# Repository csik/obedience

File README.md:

# obedience

Hacking around an aestheticized experiment.

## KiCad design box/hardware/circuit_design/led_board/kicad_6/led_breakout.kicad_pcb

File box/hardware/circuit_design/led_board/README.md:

# LED Driver Board Set

### Meant to be used as a set of two identical boards
- Each board can drive up to 16 LEDs
- The first board connects to the Raspberry Pi
- The second is daisy chained with a jumper
- Besides the 30 main Milgram voltage LEDs, 2 auxilliary LEDs are available on the second board
- A small `3V3 OK` LED on the board illuminates when the board has power

### An optional `VBUS` connection is available for driving the LEDS with a different DC voltage source
- Select the DC voltage source with a solder jumper
- The `3V3` setting is typical
- The `VBUS` setting is included in case there are issues with driving the LEDs from the Raspberry Pi power supply
- Note that the `VBUS OK` LED will only light up if there is a DC source connected to `VBUS`
  - it is normal for this LED to be dim if using the `3V3` DC source

### View from the back

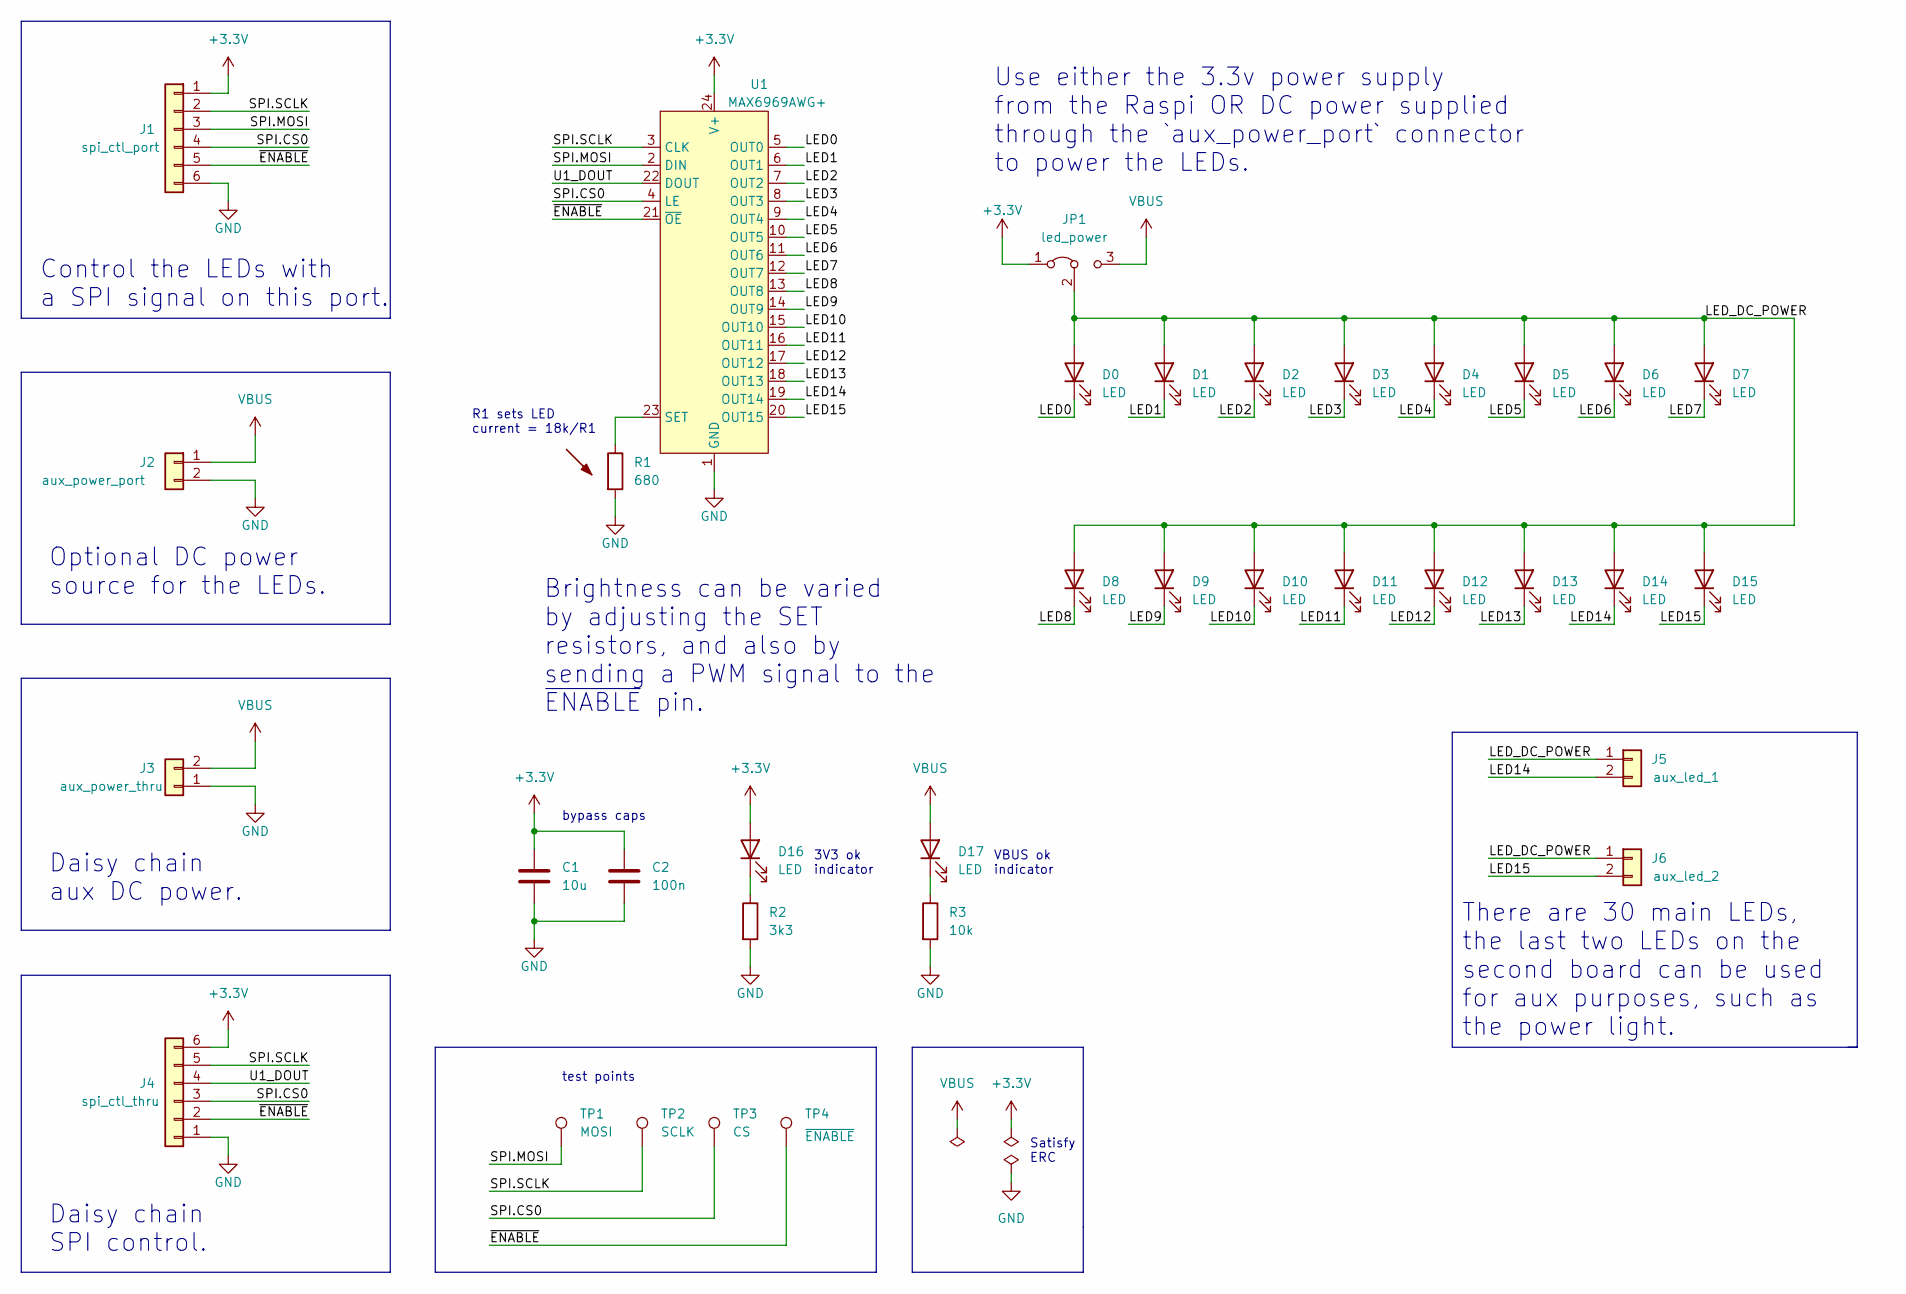
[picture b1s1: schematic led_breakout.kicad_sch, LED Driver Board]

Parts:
C1: 10u; C_0805_2012Metric
C2: 100n; C_0805_2012Metric
D0, D1, D2, D3, D4, D5, D6, D7, D8, D9, D10, D11, D12, D13, D14, D15: LED; LED_D5.0mm
D16, D17: LED; LED_0805_2012Metric
J1: spi_ctl_port; Molex_KK-254_AE-6410-06A_1x06_P2.54mm_Vertical
J2: aux_power_port; Molex_KK-254_AE-6410-02A_1x02_P2.54mm_Vertical
J3: aux_power_thru; Molex_KK-254_AE-6410-02A_1x02_P2.54mm_Vertical
J4: spi_ctl_thru; Molex_KK-254_AE-6410-06A_1x06_P2.54mm_Vertical
J5: aux_led_1; Molex_KK-254_AE-6410-02A_1x02_P2.54mm_Vertical
J6: aux_led_2; Molex_KK-254_AE-6410-02A_1x02_P2.54mm_Vertical
JP1: led_power; SolderJumper-3_P2.0mm_Open_TrianglePad1.0x1.5mm
R1: 680; R_0805_2012Metric
R2: 3k3; R_0805_2012Metric
R3: 10k; R_0805_2012Metric
TP1: MOSI; TestPoint_Keystone_5000-5004_Miniature
TP2: SCLK; TestPoint_Keystone_5000-5004_Miniature
TP3: CS; TestPoint_Keystone_5000-5004_Miniature
TP4: ~{ENABLE}; TestPoint_Keystone_5000-5004_Miniature
U1: MAX6969AWG+; SOIC-24W_7.5x15.4mm_P1.27mm

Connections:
+3.3V: C1.1, C2.1, D16.2 (A), J1.1, J4.6, JP1.1 (A), U1.24 (V+)
/LED0: D0.1 (K), U1.5 (OUT0)
/LED1: D1.1 (K), U1.6 (OUT1)
/LED2: D2.1 (K), U1.7 (OUT2)
/LED3: D3.1 (K), U1.8 (OUT3)
/LED4: D4.1 (K), U1.9 (OUT4)
/LED5: D5.1 (K), U1.10 (OUT5)
/LED6: D6.1 (K), U1.11 (OUT6)
/LED7: D7.1 (K), U1.12 (OUT7)
/LED8: D8.1 (K), U1.13 (OUT8)
/LED9: D9.1 (K), U1.14 (OUT9)
/LED10: D10.1 (K), U1.15 (OUT10)
/LED11: D11.1 (K), U1.16 (OUT11)
/LED12: D12.1 (K), U1.17 (OUT12)
/LED13: D13.1 (K), U1.18 (OUT13)
/LED14: D14.1 (K), J5.2, U1.19 (OUT14)
/LED15: D15.1 (K), J6.2, U1.20 (OUT15)
/LED_DC_POWER: D0.2 (A), D1.2 (A), D2.2 (A), D3.2 (A), D4.2 (A), D5.2 (A), D6.2 (A), D7.2 (A), D8.2 (A), D9.2 (A), D10.2 (A), D11.2 (A), D12.2 (A), D13.2 (A), D14.2 (A), D15.2 (A), J5.1, J6.1, JP1.2 (C)
/SPI.CS0: J1.4, J4.3, TP3.1, U1.4 (LE)
/SPI.MOSI: J1.3, TP1.1, U1.2 (DIN)
/SPI.SCLK: J1.2, J4.5, TP2.1, U1.3 (CLK)
/U1_DOUT: J4.4, U1.22 (DOUT)
/~ENABLE: J1.5, J4.2, TP4.1, U1.21 (~OE)
GND: C1.2, C2.2, J1.6, J2.2, J3.1, J4.1, R1.2, R2.2, R3.2, U1.1 (GND)
unnamed: D16.1 (K), R2.1
unnamed: D17.1 (K), R3.1
unnamed: R1.1, U1.23 (SET)
VBUS: D17.2 (A), J2.1, J3.2, JP1.3 (B)

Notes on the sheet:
R1 sets LED current = 18k/R1
3V3 ok indicator
Optional DC power source for the LEDs.
There are 30 main LEDs, the last two LEDs on the second board can be used for aux purposes, such as the power light.
Brightness can be varied by adjusting the SET resistors, and also by sending a PWM signal to the ~{ENABLE} pin.
Use either the 3.3v power supply from the Raspi OR DC power supplied through the `aux_power_port` connector to power the LEDs.
bypass caps
Control the LEDs with a SPI signal on this port.
Daisy chain aux DC power.
Satisfy ERC
test points
Daisy chain SPI control.
VBUS ok indicator

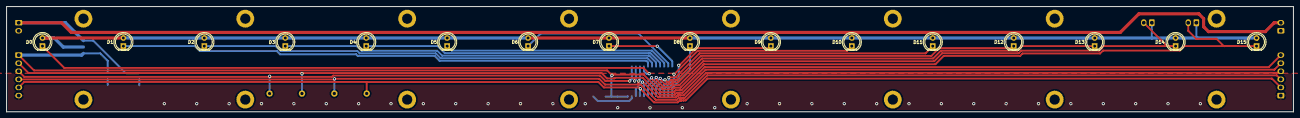
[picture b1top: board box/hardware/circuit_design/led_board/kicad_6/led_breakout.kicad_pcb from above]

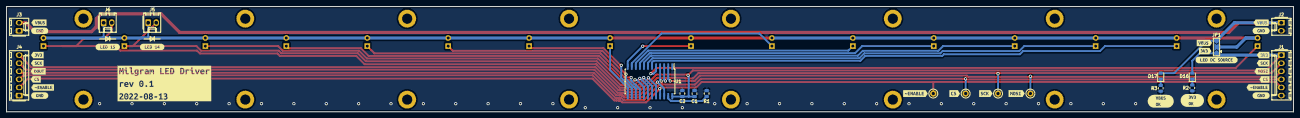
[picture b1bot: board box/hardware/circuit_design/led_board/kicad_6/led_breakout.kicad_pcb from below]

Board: 2 copper layers, 403.9 x 33.0 mm, 63 parts (47 on the bottom side), 28 nets.

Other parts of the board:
kibuzzard-62C08D9D: G***; kibuzzard-62C08D9D
kibuzzard-62C08DB4: G***; kibuzzard-62C08DB4
kibuzzard-62C080C4, kibuzzard-62C080C4#2, kibuzzard-62C080C4#3, kibuzzard-62C080C4#4: G***; kibuzzard-62C080C4
kibuzzard-62C080FF, kibuzzard-62C080FF#2: G***; kibuzzard-62C080FF
kibuzzard-62C081B4, kibuzzard-62C081B4#2: G***; kibuzzard-62C081B4
kibuzzard-62C081F9: G***; kibuzzard-62C081F9
kibuzzard-62C098AA: G***; kibuzzard-62C098AA
kibuzzard-62C098B9: G***; kibuzzard-62C098B9
kibuzzard-62C0819F, kibuzzard-62C0819F#2: G***; kibuzzard-62C0819F
kibuzzard-62C0832C: G***; kibuzzard-62C0832C
kibuzzard-62C0833D: G***; kibuzzard-62C0833D
kibuzzard-62C08177, kibuzzard-62C08177#2: G***; kibuzzard-62C08177
kibuzzard-62C08184, kibuzzard-62C08184#2: G***; kibuzzard-62C08184
kibuzzard-62C08194: G***; kibuzzard-62C08194
kibuzzard-62C08351: G***; kibuzzard-62C08351
kibuzzard-62F7B6AB: G***; kibuzzard-62F7B6AB
kibuzzard-62F7B6F0: G***; kibuzzard-62F7B6F0
kibuzzard-62F7B661: G***; kibuzzard-62F7B661
kibuzzard-62F7B788: G***; kibuzzard-62F7B788
kibuzzard-62F7B810: G***; kibuzzard-62F7B810

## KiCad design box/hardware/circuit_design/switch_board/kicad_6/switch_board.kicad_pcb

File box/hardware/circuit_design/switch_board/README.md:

# Switch Reader Board Set

### Meant to be used as a set of two identical boards
- Each board can read up to 16 switches
- The first board connects to the Raspberry Pi
- The second is daisy chained with a jumper
- Besides the 30 main Milgram voltage switches, 4 auxilliary switches are available on the second board
- A small `3V3 OK` LED on the board illuminates when the board has power
- Note that you don't need to solder every switch lug, only 1 of the switch poles is wired

### The I2C addresses must be set with solder jumpers
- These jumpers make up the low 3-bits of the binary address for each PC9555 chip
- The most likely pattern, looking from left to right is: `0b010, 0b011, 0b000, 0b001`
  - this matches the addresses in the demo function of `[0x20, 0x21, 0x22, 0x23]`
- Valid addresses for the chips are in `[0x20..0x27]`
  - the `2` in the upper byte is fixed, and the lower byte can be changed 
- Other addresses are possible if more I2C devices are added and there is an address collision

### View from the back

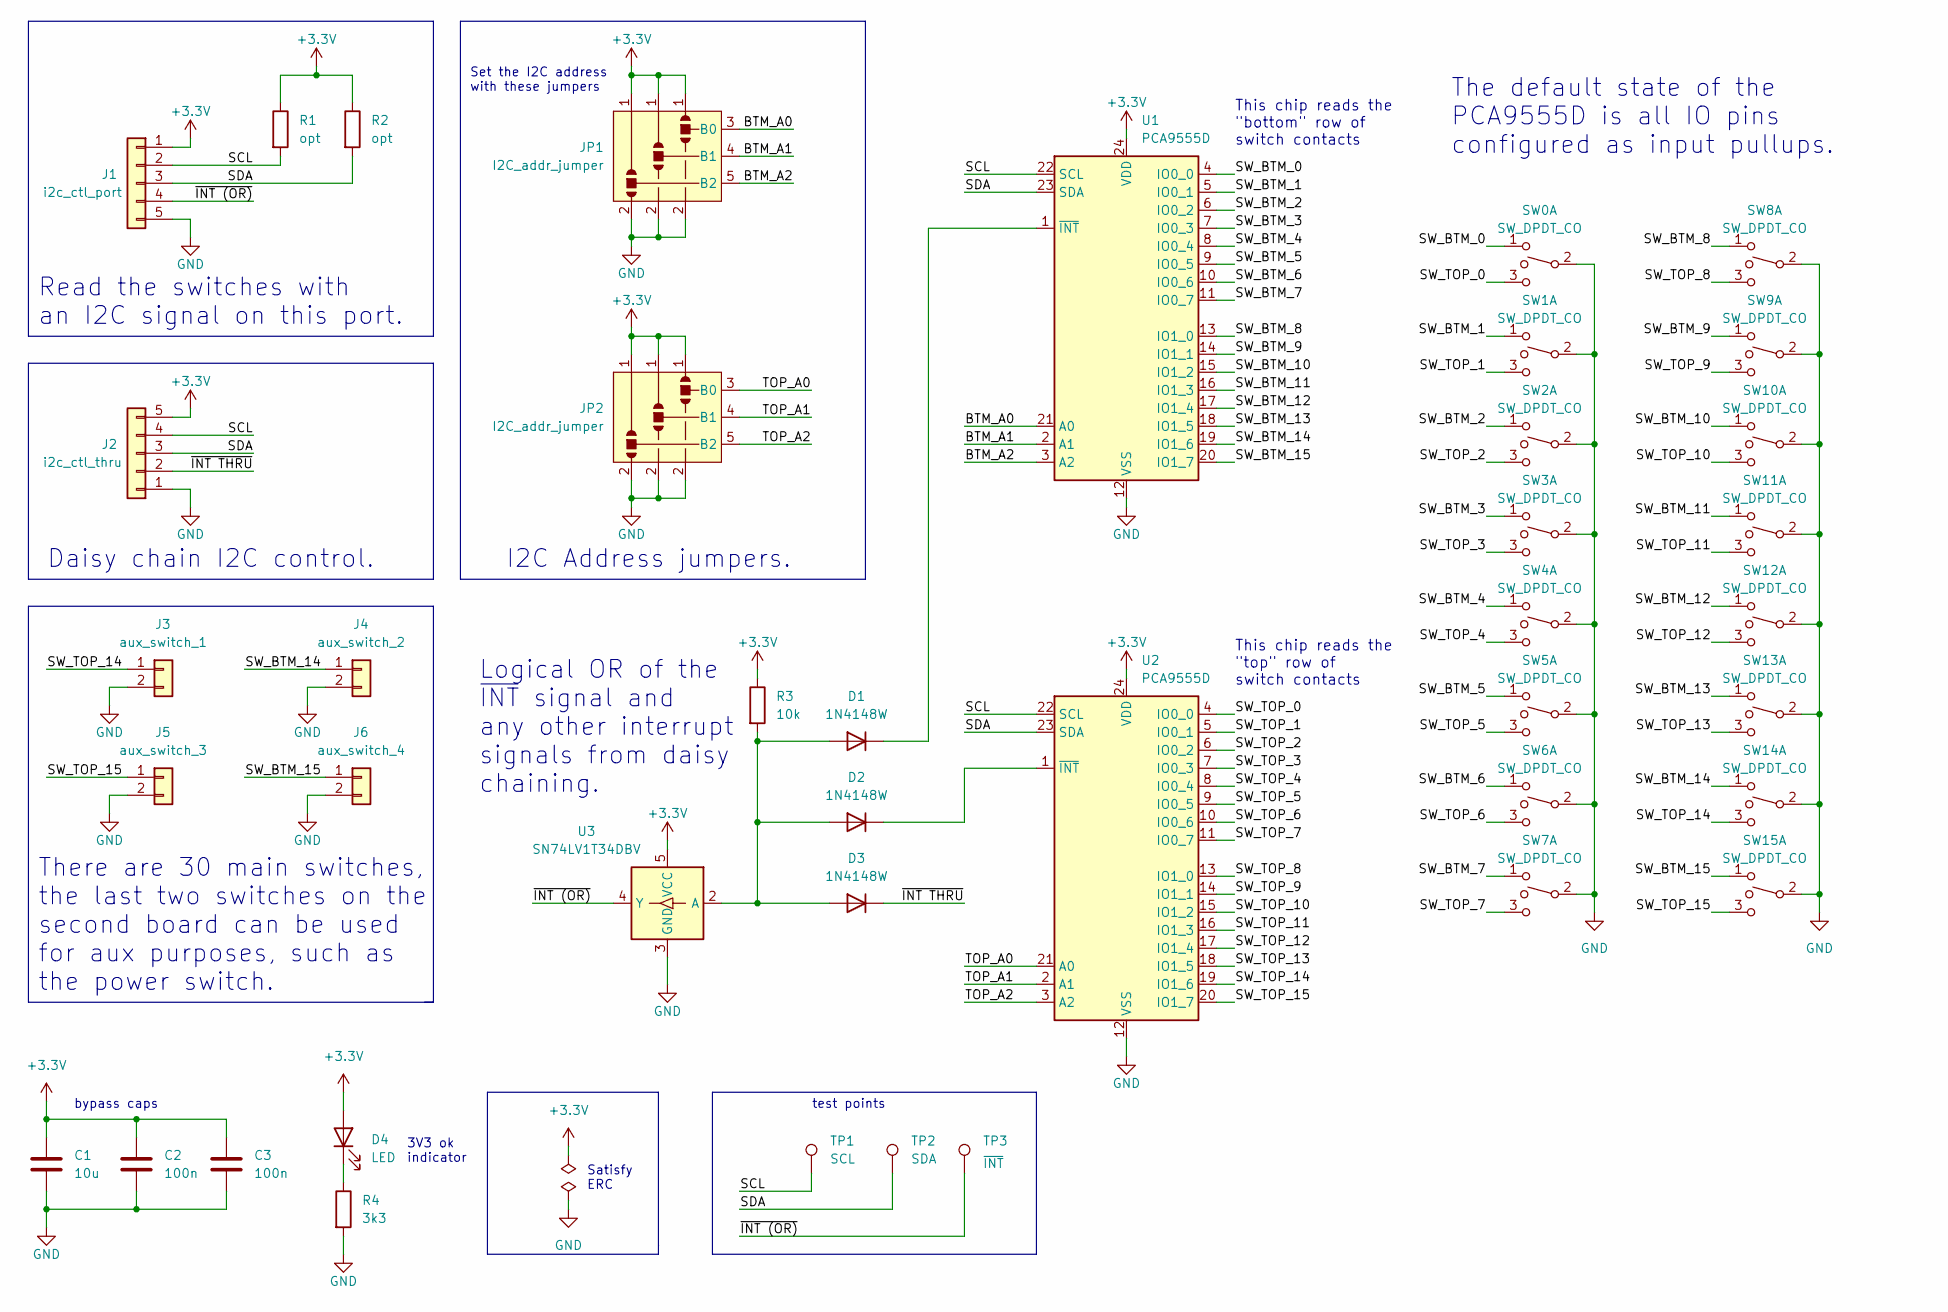
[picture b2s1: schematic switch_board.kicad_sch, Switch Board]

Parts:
C1: 10u; C_0805_2012Metric
C2, C3: 100n; C_0805_2012Metric
D1, D2, D3: 1N4148W; D_SOD-123
D4: LED; LED_0805_2012Metric
J1: i2c_ctl_port; Molex_KK-254_AE-6410-05A_1x05_P2.54mm_Vertical
J2: i2c_ctl_thru; Molex_KK-254_AE-6410-05A_1x05_P2.54mm_Vertical
J3: aux_switch_1; Molex_KK-254_AE-6410-02A_1x02_P2.54mm_Vertical
J4: aux_switch_2; Molex_KK-254_AE-6410-02A_1x02_P2.54mm_Vertical
J5: aux_switch_3; Molex_KK-254_AE-6410-02A_1x02_P2.54mm_Vertical
J6: aux_switch_4; Molex_KK-254_AE-6410-02A_1x02_P2.54mm_Vertical
JP1, JP2: I2C_addr_jumper
R1, R2: opt; R_0805_2012Metric
R3: 10k; R_0805_2012Metric
R4: 3k3; R_0805_2012Metric
SW0, SW1, SW2, SW3, SW4, SW5, SW6, SW7, SW8, SW9, SW10, SW11, SW12, SW13, SW14, SW15: SW_DPDT_CO; orange_DPDT
TP1: SCL; TestPoint_Keystone_5000-5004_Miniature
TP2: SDA; TestPoint_Keystone_5000-5004_Miniature
TP3: ~{INT}; TestPoint_Keystone_5000-5004_Miniature
U1, U2: PCA9555D; SOIC-24W_7.5x15.4mm_P1.27mm
U3: SN74LV1T34DBV; SOT-23-5

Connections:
+3.3V: C1.1, C2.1, C3.1, D4.2 (A), J1.1, J2.5, JP1.1, JP2.1, R1.1, R2.1, R3.1, U1.24 (VDD), U2.24 (VDD), U3.5 (VCC)
/BTM_A0: JP1.3 (B0), U1.21 (A0)
/BTM_A1: JP1.4 (B1), U1.2 (A1)
/BTM_A2: JP1.5 (B2), U1.3 (A2)
/SCL: J1.2, J2.4, R1.2, TP1.1, U1.22 (SCL), U2.22 (SCL)
/SDA: J1.3, J2.3, R2.2, TP2.1, U1.23 (SDA), U2.23 (SDA)
/SW_BTM_0: SW0.1, U1.4 (IO0_0)
/SW_BTM_1: SW1.1, U1.5 (IO0_1)
/SW_BTM_2: SW2.1, U1.6 (IO0_2)
/SW_BTM_3: SW3.1, U1.7 (IO0_3)
/SW_BTM_4: SW4.1, U1.8 (IO0_4)
/SW_BTM_5: SW5.1, U1.9 (IO0_5)
/SW_BTM_6: SW6.1, U1.10 (IO0_6)
/SW_BTM_7: SW7.1, U1.11 (IO0_7)
/SW_BTM_8: SW8.1, U1.13 (IO1_0)
/SW_BTM_9: SW9.1, U1.14 (IO1_1)
/SW_BTM_10: SW10.1, U1.15 (IO1_2)
/SW_BTM_11: SW11.1, U1.16 (IO1_3)
/SW_BTM_12: SW12.1, U1.17 (IO1_4)
/SW_BTM_13: SW13.1, U1.18 (IO1_5)
/SW_BTM_14: J4.1, SW14.1, U1.19 (IO1_6)
/SW_BTM_15: J6.1, SW15.1, U1.20 (IO1_7)
/SW_TOP_0: SW0.3, U2.4 (IO0_0)
/SW_TOP_1: SW1.3, U2.5 (IO0_1)
/SW_TOP_2: SW2.3, U2.6 (IO0_2)
/SW_TOP_3: SW3.3, U2.7 (IO0_3)
/SW_TOP_4: SW4.3, U2.8 (IO0_4)
/SW_TOP_5: SW5.3, U2.9 (IO0_5)
/SW_TOP_6: SW6.3, U2.10 (IO0_6)
/SW_TOP_7: SW7.3, U2.11 (IO0_7)
/SW_TOP_8: SW8.3, U2.13 (IO1_0)
/SW_TOP_9: SW9.3, U2.14 (IO1_1)
/SW_TOP_10: SW10.3, U2.15 (IO1_2)
/SW_TOP_11: SW11.3, U2.16 (IO1_3)
/SW_TOP_12: SW12.3, U2.17 (IO1_4)
/SW_TOP_13: SW13.3, U2.18 (IO1_5)
/SW_TOP_14: J3.1, SW14.3, U2.19 (IO1_6)
/SW_TOP_15: J5.1, SW15.3, U2.20 (IO1_7)
/TOP_A0: JP2.3 (B0), U2.21 (A0)
/TOP_A1: JP2.4 (B1), U2.2 (A1)
/TOP_A2: JP2.5 (B2), U2.3 (A2)
/~INT (OR): J1.4, TP3.1, U3.4 (Y)
/~INT THRU: D3.1 (K), J2.2
GND: C1.2, C2.2, C3.2, J1.5, J2.1, J3.2, J4.2, J5.2, J6.2, JP1.2, JP2.2, R4.2, SW0.2, SW1.2, SW2.2, SW3.2, SW4.2, SW5.2, SW6.2, SW7.2, SW8.2, SW9.2, SW10.2, SW11.2, SW12.2, SW13.2, SW14.2, SW15.2, U1.12 (VSS), U2.12 (VSS), U3.3 (GND)
unnamed: D1.1 (K), U1.1 (~INT)
unnamed: D1.2 (A), D2.2 (A), D3.2 (A), R3.2, U3.2 (A)
unnamed: D2.1 (K), U2.1 (~INT)
unnamed: D4.1 (K), R4.1

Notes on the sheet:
I2C Address jumpers.
3V3 ok indicator
Set the I2C address with these jumpers
This chip reads the "top" row of switch contacts
This chip reads the "bottom" row of switch contacts
bypass caps
Read the switches with an I2C signal on this port.
Satisfy ERC
The default state of the PCA9555D is all IO pins configured as input pullups.
Logical OR of the ~{INT} signal and any other interrupt signals from daisy chaining.
There are 30 main switches, the last two switches on the second board can be used for aux purposes, such as the power switch.
test points
Daisy chain I2C control.

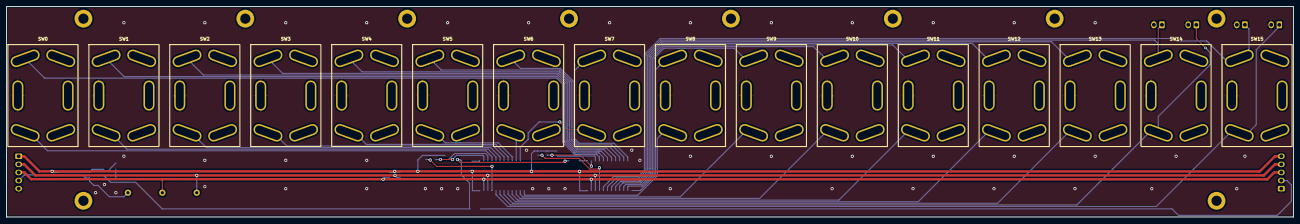
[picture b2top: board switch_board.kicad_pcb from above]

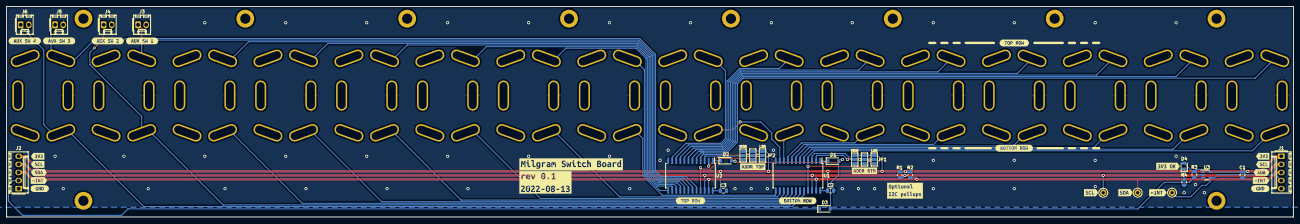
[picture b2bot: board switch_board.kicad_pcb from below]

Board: 2 copper layers, 403.9 x 66.0 mm, 75 parts (52 on the bottom side), 48 nets.

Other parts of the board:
1, 2, 3, 4, 5, 6, 7: (no value)
kibuzzard-62CDA3AF, kibuzzard-62CDA3AF#2: G***; kibuzzard-62CDA3AF
kibuzzard-62CDA3C3, kibuzzard-62CDA3C3#2: G***; kibuzzard-62CDA3C3
kibuzzard-62CDA3D5, kibuzzard-62CDA3D5#2: G***; kibuzzard-62CDA3D5
kibuzzard-62CDA3FA, kibuzzard-62CDA3FA#2: G***; kibuzzard-62CDA3FA
kibuzzard-62CDA40B, kibuzzard-62CDA40B#2: G***; kibuzzard-62CDA40B
kibuzzard-62CDB34A, kibuzzard-62CDB34A#2: G***; kibuzzard-62CDB34A
kibuzzard-62CDB49B: G***; kibuzzard-62CDB49B
kibuzzard-62CDB376, kibuzzard-62CDB376#2: G***; kibuzzard-62CDB376
kibuzzard-62CDB476: G***; kibuzzard-62CDB476
kibuzzard-62D2CEAF: G***; kibuzzard-62D2CEAF
kibuzzard-62E2A96C: G***; kibuzzard-62E2A96C
kibuzzard-62E2A97A: G***; kibuzzard-62E2A97A
kibuzzard-62E2A98A: G***; kibuzzard-62E2A98A
kibuzzard-62E2A810: G***; kibuzzard-62E2A810
kibuzzard-62E2AEDB: G***; kibuzzard-62E2AEDB
kibuzzard-62F7BFC3: G***; kibuzzard-62F7BFC3
kibuzzard-62F7F1A0: G***; kibuzzard-62F7F1A0
kibuzzard-62F7F1AD: G***; kibuzzard-62F7F1AD
kibuzzard-62F7F16A: G***; kibuzzard-62F7F16A
kibuzzard-62F7F17D: G***; kibuzzard-62F7F17D

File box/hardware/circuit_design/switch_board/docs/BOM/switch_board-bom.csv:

Row,Description,Part,References,Value,Footprint,Quantity Per PCB,Status,Datasheet
1,Unpolarized capacitor,C,C2 C3,100n,C_0805_2012Metric,2, ,~
2,Unpolarized capacitor,C,C1,10u,C_0805_2012Metric,1, ,~
3,"75V 0.15A Fast Switching Diode, SOD-123",1N4148W,D1 D2 D3,1N4148W,D_SOD-123,3, ,https://www.vishay.com/docs/85748/1n4148w.pdf
4,Light emitting diode,LED,D4,LED,LED_0805_2012Metric,1, ,~
5,"Generic connector, single row, 01x02, script generated (kicad-library-utils/schlib/autogen/connector/)",Conn_01x02,J3 J4 J5 J6,aux_switch_1,Molex_KK-254_AE-6410-02A_1x02_P2.54mm_Vertical,4, ,~
6,"Generic connector, single row, 01x05, script generated (kicad-library-utils/schlib/autogen/connector/)",Conn_01x05,J1 J2,i2c_ctl_port,Molex_KK-254_AE-6410-05A_1x05_P2.54mm_Vertical,2, ,~
7,,I2C_addr_jumper,JP1 JP2,I2C_addr_jumper,I2C_addr_jumper,2, ,
8,Resistor,R,R4,3k3,R_0805_2012Metric,1, ,~
9,Resistor,R,R3,10k,R_0805_2012Metric,1, ,~
10,Resistor,R,R1 R2,opt,R_0805_2012Metric,2, ,~
11,"Switch, single pole double throw, center OFF position",SW_DPDT_CO,SW0 SW1 SW2 SW3 SW4 SW5 SW6 SW7 SW8 SW9 SW10 SW11 SW12 SW13 SW14 SW15,SW_DPDT_CO,orange_DPDT,16, ,~
12,"IO expander 16 GPIO, I2C 400kHz, Interrupt, 2.3 - 5.5V, SOIC-24",PCA9555D,U1 U2,PCA9555D,SOIC-24W_7.5x15.4mm_P1.27mm,2, ,https://www.nxp.com/docs/en/data-sheet/PCA9555.pdf
13,"Single Power Supply, Single Buffer GATE, CMOS Logic, Level Shifter, SOT-23-5",SN74LV1T34DBV,U3,SN74LV1T34DBV,SOT-23-5,1, ,https://www.ti.com/lit/ds/symlink/sn74lv1t34.pdf





Project info:
Schematic:,switch_board
Variant:,default
Revision:,0.1
Date:,2022-08-13
KiCad Version:,6.0.5+dfsg-1~bpo11+1
Statistics:
Component Groups:,13
Component Count:,38 (14 SMD/ 22 THT)
Fitted Components:,38 (14 SMD/ 22 THT)
Number of PCBs:,1
Total Components:,38

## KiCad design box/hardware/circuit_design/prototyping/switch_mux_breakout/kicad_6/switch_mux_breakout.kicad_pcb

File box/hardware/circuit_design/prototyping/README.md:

# Breakout Boards for Prototyping and Testing Functionality of the User Interface

## The Obedience Box User Interface consists of three main components:
- 30 switches
- 30 LEDs
- An analog voltmeter

## This directory contains small breakout boards used to test out these systems

### Each subdirectory has all the files needed to:
- edit the schematic and pcb layout using KiCad 6
- construct the board (pdf schematic, BOM, gerbers)
- test the board with a python script

### In the testing phase, upload and run the python test script on a Raspberry Pi with wires connected to the breakout boards as needed

### Expect these boards to be a work in progress as we hone in on the final circuit design

### See the individual breakout board directories for further information

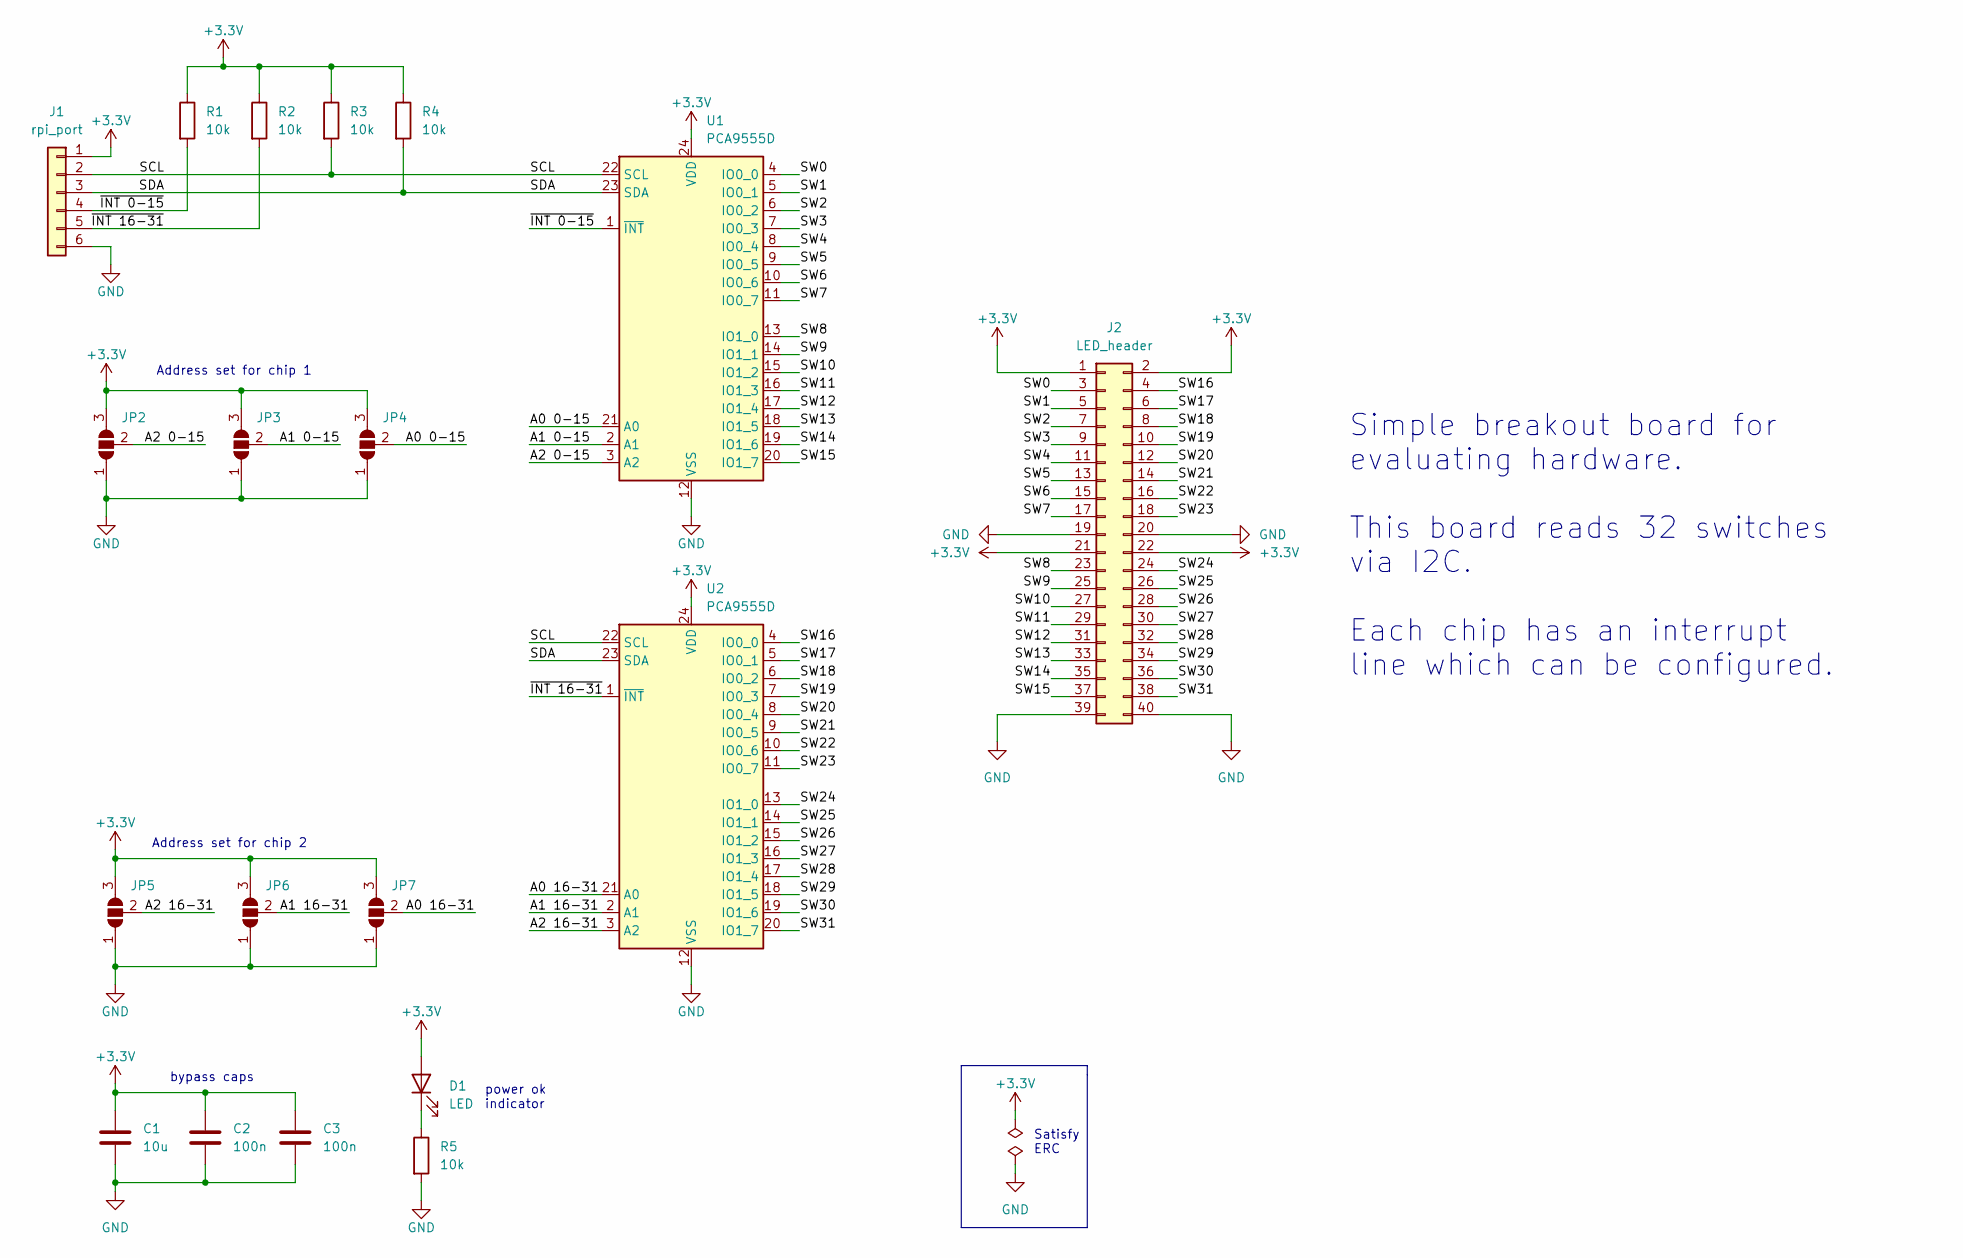
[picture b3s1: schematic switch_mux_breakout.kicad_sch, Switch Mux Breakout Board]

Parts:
C1: 10u; C_0805_2012Metric
C2, C3: 100n; C_0805_2012Metric
D1: LED; LED_0805_2012Metric
J1: rpi_port; PinHeader_1x06_P2.54mm_Vertical
J2: LED_header; PinHeader_2x20_P2.54mm_Vertical
JP2, JP3, JP4, JP5, JP6, JP7: SolderJumper_3_Open; SolderJumper-3_P1.3mm_Open_Pad1.0x1.5mm
R1, R2, R3, R4, R5: 10k; R_0805_2012Metric
U1, U2: PCA9555D; SOIC-24W_7.5x15.4mm_P1.27mm

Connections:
+3V3: C1.1, C2.1, C3.1, D1.2 (A), J1.1, J2.1, J2.2, J2.21, J2.22, JP2.3 (B), JP3.3 (B), JP4.3 (B), JP5.3 (B), JP6.3 (B), JP7.3 (B), R1.1, R2.1, R3.1, R4.1, U1.24 (VDD), U2.24 (VDD)
/A0 0-15: JP4.2 (C), U1.21 (A0)
/A0 16-31: JP7.2 (C), U2.21 (A0)
/A1 0-15: JP3.2 (C), U1.2 (A1)
/A1 16-31: JP6.2 (C), U2.2 (A1)
/A2 0-15: JP2.2 (C), U1.3 (A2)
/A2 16-31: JP5.2 (C), U2.3 (A2)
/SCL: J1.2, R3.2, U1.22 (SCL), U2.22 (SCL)
/SDA: J1.3, R4.2, U1.23 (SDA), U2.23 (SDA)
/SW0: J2.3, U1.4 (IO0_0)
/SW1: J2.5, U1.5 (IO0_1)
/SW2: J2.7, U1.6 (IO0_2)
/SW3: J2.9, U1.7 (IO0_3)
/SW4: J2.11, U1.8 (IO0_4)
/SW5: J2.13, U1.9 (IO0_5)
/SW6: J2.15, U1.10 (IO0_6)
/SW7: J2.17, U1.11 (IO0_7)
/SW8: J2.23, U1.13 (IO1_0)
/SW9: J2.25, U1.14 (IO1_1)
/SW10: J2.27, U1.15 (IO1_2)
/SW11: J2.29, U1.16 (IO1_3)
/SW12: J2.31, U1.17 (IO1_4)
/SW13: J2.33, U1.18 (IO1_5)
/SW14: J2.35, U1.19 (IO1_6)
/SW15: J2.37, U1.20 (IO1_7)
/SW16: J2.4, U2.4 (IO0_0)
/SW17: J2.6, U2.5 (IO0_1)
/SW18: J2.8, U2.6 (IO0_2)
/SW19: J2.10, U2.7 (IO0_3)
/SW20: J2.12, U2.8 (IO0_4)
/SW21: J2.14, U2.9 (IO0_5)
/SW22: J2.16, U2.10 (IO0_6)
/SW23: J2.18, U2.11 (IO0_7)
/SW24: J2.24, U2.13 (IO1_0)
/SW25: J2.26, U2.14 (IO1_1)
/SW26: J2.28, U2.15 (IO1_2)
/SW27: J2.30, U2.16 (IO1_3)
/SW28: J2.32, U2.17 (IO1_4)
/SW29: J2.34, U2.18 (IO1_5)
/SW30: J2.36, U2.19 (IO1_6)
/SW31: J2.38, U2.20 (IO1_7)
/~INT 0-15: J1.4, R1.2, U1.1 (~INT)
/~INT 16-31: J1.5, R2.2, U2.1 (~INT)
GND: C1.2, C2.2, C3.2, J1.6, J2.19, J2.20, J2.39, J2.40, JP2.1 (A), JP3.1 (A), JP4.1 (A), JP5.1 (A), JP6.1 (A), JP7.1 (A), R5.2, U1.12 (VSS), U2.12 (VSS)
unnamed: D1.1 (K), R5.1

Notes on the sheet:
bypass caps
Simple breakout board for evaluating hardware. This board reads 32 switches via I2C. Each chip has an interrupt line which can be configured.
power ok indicator
Address set for chip 1
Satisfy ERC
Address set for chip 2

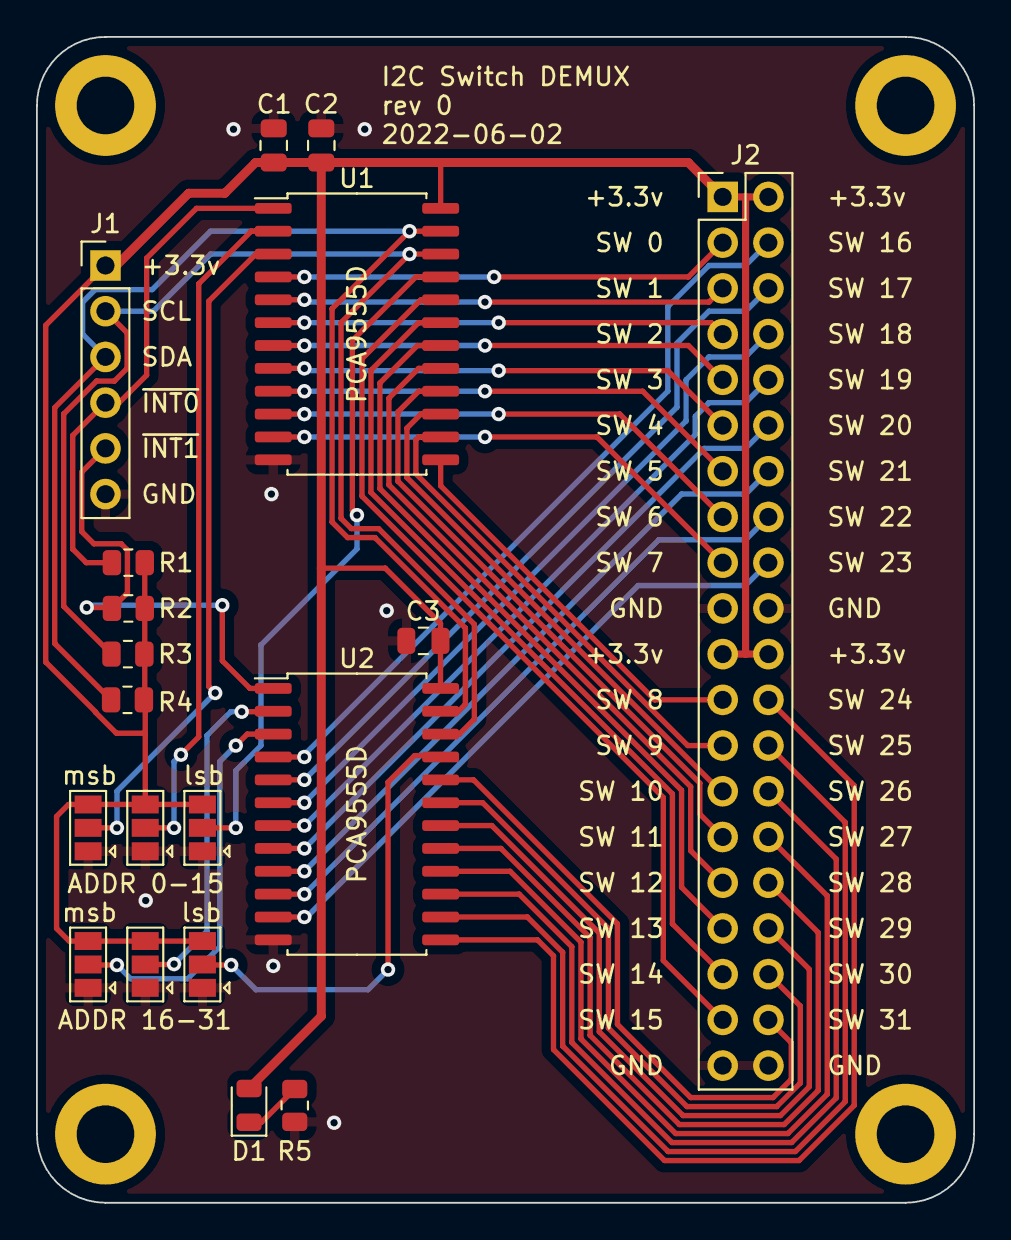
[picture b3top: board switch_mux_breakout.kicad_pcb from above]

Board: 2 copper layers, 52.1 x 64.8 mm, 19 parts (0 on the bottom side), 45 nets.

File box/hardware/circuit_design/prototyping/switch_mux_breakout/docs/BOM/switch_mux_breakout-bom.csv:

Row,Description,Part,References,Value,Footprint,Quantity Per PCB,Status,Datasheet
1,Unpolarized capacitor,C,C2 C3,100n,C_0805_2012Metric,2, ,~
2,Unpolarized capacitor,C,C1,10u,C_0805_2012Metric,1, ,~
3,Light emitting diode,LED,D1,LED,LED_0805_2012Metric,1, ,~
4,"Generic connector, double row, 02x20, odd/even pin numbering scheme (row 1 odd numbers, row 2 even numbers), script generated (kicad-library-utils/schlib/autogen/connector/)",Conn_02x20_Odd_Even,J2,LED_header,PinHeader_2x20_P2.54mm_Vertical,1, ,~
5,"Generic connector, single row, 01x06, script generated (kicad-library-utils/schlib/autogen/connector/)",Conn_01x06,J1,rpi_port,PinHeader_1x06_P2.54mm_Vertical,1, ,~
6,Resistor,R,R1 R2 R3 R4 R5,10k,R_0805_2012Metric,5, ,~
7,"IO expander 16 GPIO, I2C 400kHz, Interrupt, 2.3 - 5.5V, SOIC-24",PCA9555D,U1 U2,PCA9555D,SOIC-24W_7.5x15.4mm_P1.27mm,2, ,https://www.nxp.com/docs/en/data-sheet/PCA9555.pdf





Project info:
Schematic:,switch_mux_breakout
Variant:,default
Revision:,0
Date:,2022-06-02
KiCad Version:,6.0.6-3a73a75311~116~ubuntu22.04.1
Statistics:
Component Groups:,7
Component Count:,13 (11 SMD/ 2 THT)
Fitted Components:,13 (11 SMD/ 2 THT)
Number of PCBs:,1
Total Components:,13

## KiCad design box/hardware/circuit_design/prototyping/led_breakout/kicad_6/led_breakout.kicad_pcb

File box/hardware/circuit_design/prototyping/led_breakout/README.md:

# LED Driver Breakout Board

## Small pcb to test the LED driver circuit

## Brief description:
Two MAX6969 LED driver chips are driven by SPI.

Open `index.html` in a browser for easy to navigate documentation and fabrication files.

## Status of the project:

Task | Status |
---------|--------------|
Schematic capture | &#9745;
PCB layout | &#9745;
Test build | &#9745;
Safe to order boards| &#9745;
Python test script | &#9745;

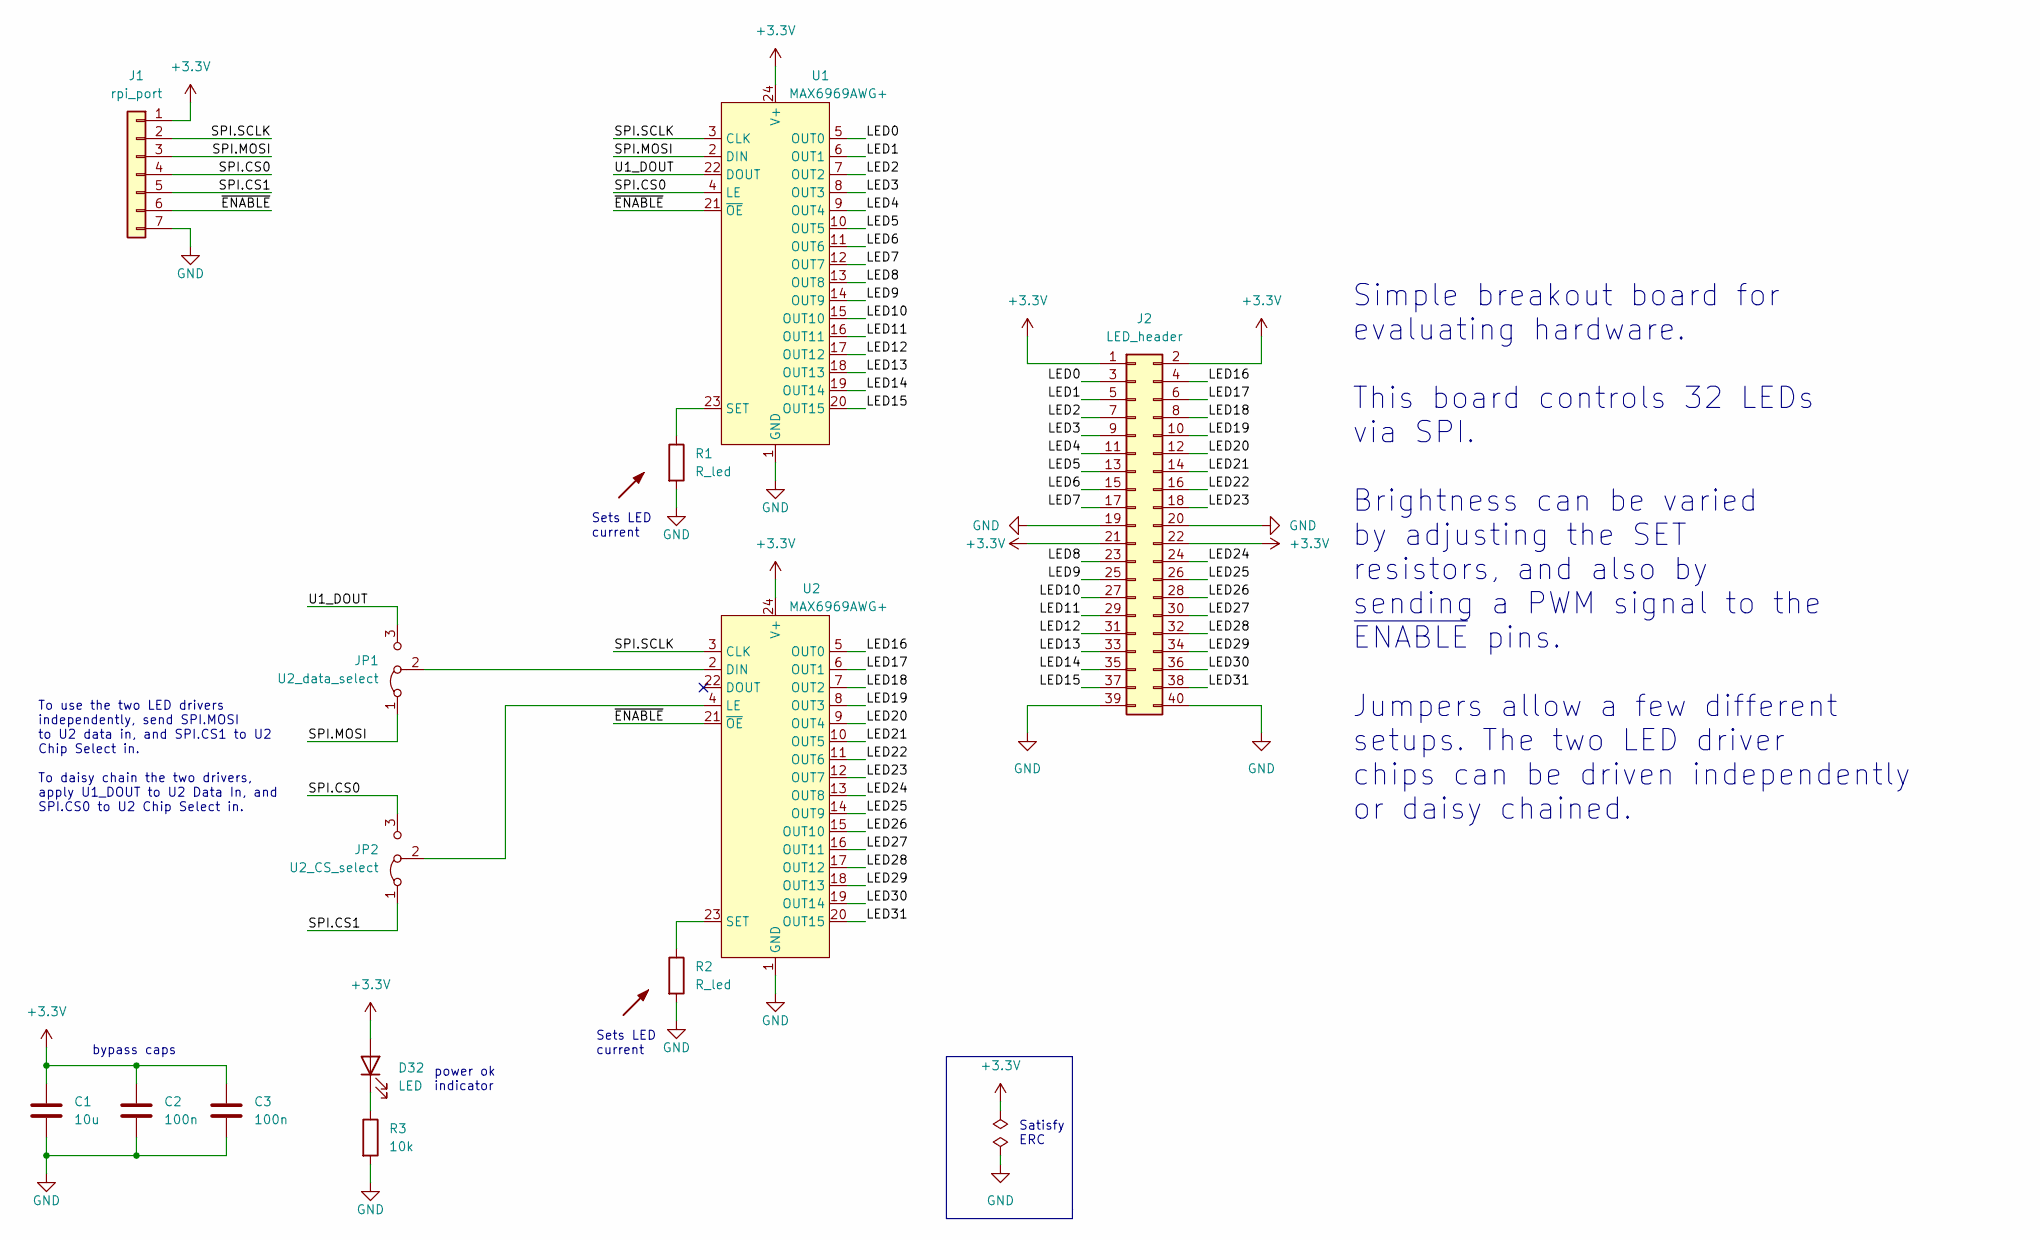
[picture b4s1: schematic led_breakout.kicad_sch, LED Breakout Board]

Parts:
C1: 10u; C_0805_2012Metric
C2, C3: 100n; C_0805_2012Metric
D32: LED; LED_0805_2012Metric
J1: rpi_port; PinHeader_1x07_P2.54mm_Vertical
J2: LED_header; PinHeader_2x20_P2.54mm_Vertical
JP1: U2_data_select; PinHeader_1x03_P2.54mm_Vertical
JP2: U2_CS_select; PinHeader_1x03_P2.54mm_Vertical
R1, R2: R_led; R_0805_2012Metric
R3: 10k; R_0805_2012Metric
U1, U2: MAX6969AWG+; SOIC-24W_7.5x15.4mm_P1.27mm

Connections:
+3.3V: C1.1, C2.1, C3.1, D32.2 (A), J1.1, J2.1, J2.2, J2.21, J2.22, U1.24 (V+), U2.24 (V+)
/LED0: J2.3, U1.5 (OUT0)
/LED1: J2.5, U1.6 (OUT1)
/LED2: J2.7, U1.7 (OUT2)
/LED3: J2.9, U1.8 (OUT3)
/LED4: J2.11, U1.9 (OUT4)
/LED5: J2.13, U1.10 (OUT5)
/LED6: J2.15, U1.11 (OUT6)
/LED7: J2.17, U1.12 (OUT7)
/LED8: J2.23, U1.13 (OUT8)
/LED9: J2.25, U1.14 (OUT9)
/LED10: J2.27, U1.15 (OUT10)
/LED11: J2.29, U1.16 (OUT11)
/LED12: J2.31, U1.17 (OUT12)
/LED13: J2.33, U1.18 (OUT13)
/LED14: J2.35, U1.19 (OUT14)
/LED15: J2.37, U1.20 (OUT15)
/LED16: J2.4, U2.5 (OUT0)
/LED17: J2.6, U2.6 (OUT1)
/LED18: J2.8, U2.7 (OUT2)
/LED19: J2.10, U2.8 (OUT3)
/LED20: J2.12, U2.9 (OUT4)
/LED21: J2.14, U2.10 (OUT5)
/LED22: J2.16, U2.11 (OUT6)
/LED23: J2.18, U2.12 (OUT7)
/LED24: J2.24, U2.13 (OUT8)
/LED25: J2.26, U2.14 (OUT9)
/LED26: J2.28, U2.15 (OUT10)
/LED27: J2.30, U2.16 (OUT11)
/LED28: J2.32, U2.17 (OUT12)
/LED29: J2.34, U2.18 (OUT13)
/LED30: J2.36, U2.19 (OUT14)
/LED31: J2.38, U2.20 (OUT15)
/SPI.CS0: J1.4, JP2.3 (B), U1.4 (LE)
/SPI.CS1: J1.5, JP2.1 (A)
/SPI.MOSI: J1.3, JP1.1 (A), U1.2 (DIN)
/SPI.SCLK: J1.2, U1.3 (CLK), U2.3 (CLK)
/U1_DOUT: JP1.3 (B), U1.22 (DOUT)
/~ENABLE: J1.6, U1.21 (~OE), U2.21 (~OE)
GND: C1.2, C2.2, C3.2, J1.7, J2.19, J2.20, J2.39, J2.40, R1.2, R2.2, R3.2, U1.1 (GND), U2.1 (GND)
unnamed: D32.1 (K), R3.1
unnamed: JP1.2 (C), U2.2 (DIN)
unnamed: JP2.2 (C), U2.4 (LE)
unnamed: R1.1, U1.23 (SET)
unnamed: R2.1, U2.23 (SET)

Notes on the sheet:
Sets LED current
power ok indicator
bypass caps
To use the two LED drivers independently, send SPI.MOSI to U2 data in, and SPI.CS1 to U2 Chip Select in. To daisy chain the two drivers, apply U1_DOUT to U2 Data In, and SPI.CS0 to U2 Chip Select in.
Satisfy ERC
Simple breakout board for evaluating hardware. This board controls 32 LEDs via SPI. Brightness can be varied by adjusting the SET resistors, and also by sending a PWM signal to the ~{ENABLE} pins. Jumpers allow a few different setups. The two LED driver chips can be driven independently or daisy ch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
